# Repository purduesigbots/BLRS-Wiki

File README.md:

---
description: Welcome to the public Purdue SIGBots wiki and knowledge base!
---

# Welcome!

<table data-view="cards"><thead><tr><th></th><th></th><th></th><th data-hidden data-card-cover data-type="files"></th><th data-hidden data-card-target data-type="content-ref"></th></tr></thead><tbody><tr><td></td><td>VEX Drivetrains</td><td></td><td><a href=".gitbook/assets/drive.JPG">drive.JPG</a></td><td><a href="hardware/vex-drivetrains/">vex-drivetrains</a></td></tr><tr><td></td><td>Odometry</td><td></td><td><a href=".gitbook/assets/track.jpg">track.jpg</a></td><td><a href="software/odometry.md">odometry.md</a></td></tr><tr><td></td><td>Game Analysis</td><td></td><td><a href=".gitbook/assets/images (1).jpg">images (1).jpg</a></td><td><a href="judging/notion/purdue-sigbots-notion-template/game-analysis.md">game-analysis.md</a></td></tr></tbody></table>

## Getting started with VEX Robotics?

Here on the Purdue SIGBots Wiki, you will find a place to grow your robotics knowledge. Whether you need to start a club with our [Team Financials](https://wiki.purduesigbots.com/team-administration/team-finances) article, or you want to learn some more about programming with our [Odometry](https://wiki.purduesigbots.com/software/odometry) article, there is more to learn here.

The wiki was created to host the knowledge of the VEX community with resources for competitors at all levels. It started with years of SIGBots documentation but has expanded with many open-source contributors, and new articles always being added. The wiki will stay up to date with new knowledge and continue to strengthen the articles already published.

If you are interested in contributing to the wiki feel free to open a pull request on the [wiki's repo](https://github.com/purduesigbots/BLRS-Wiki). Simply click edit on GitHub on any of the pages to see where in the repo that specific page is. We also allow contributions by PDF and Word Documents, so check it out under [contributing guidelines.](contributing-guidelines/)

If you would like to discuss or bring up an issue with the wiki without fixing it yourself, feel free to open up an issue on the aforementioned [wiki repo](https://github.com/purduesigbots/BLRS-Wiki).

<figure><figcaption><p>2024 World Champions</p></figcaption></figure>

As always if you have any questions or concerns feel free to contact us at: [sig.robotics.purdue@gmail.com](mailto:Sig.robotics.purdue@gmail.com). Please CC your coach in the email to help us assist you more effectively.

.png>)

This work is licensed under a [Creative Commons Attribution-ShareAlike 2.0 Generic License](https://creativecommons.org/licenses/by-sa/2.0/).

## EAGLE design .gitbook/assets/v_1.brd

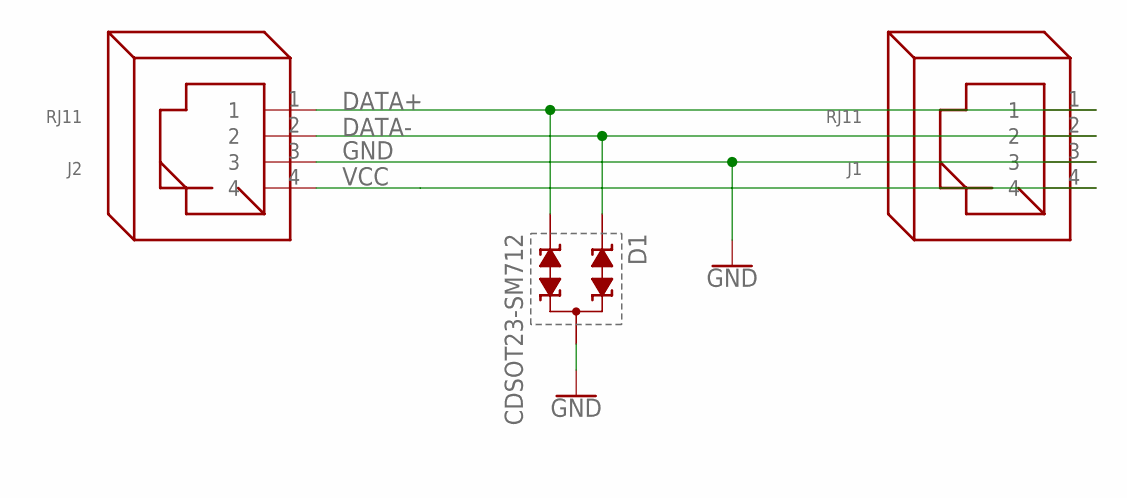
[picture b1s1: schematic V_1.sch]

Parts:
D1: CDSOT23-SM712; SOT23
J1, J2: RJ11

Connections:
DATA+: D1.2, J1.1, J2.1
DATA-: D1.1, J1.2, J2.2
GND: D1.3, J1.3, J2.3
VCC: J1.4, J2.4

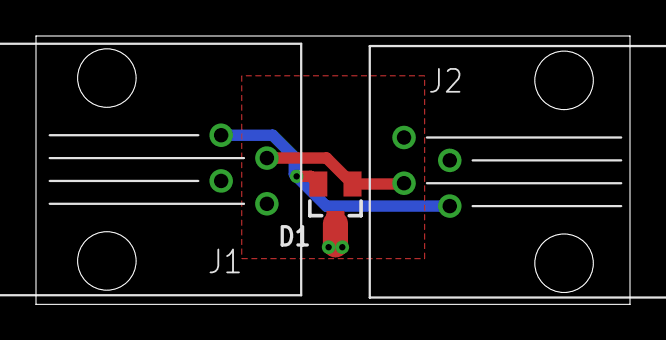
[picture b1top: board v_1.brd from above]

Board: 2 copper layers, 33.0 x 14.9 mm, 3 parts (0 on the bottom side), 4 nets.

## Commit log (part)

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2020-05-26 vex related version control info
2020-05-26 grammar
2020-05-27 GitBook: [master] 2 pages modified
2020-05-29 GitBook: [master] 4 pages and one asset modified
2020-05-29 GitBook: [master] one page modified
2020-05-29 GitBook: [master] one page and one asset modified
2020-05-29 GitBook: [master] one page and 2 assets modified
2020-06-02 Create Vex Joints
    First hardware file, explanation of four Vex joints and their uses.
2020-06-02 Add Robot Examples to Vex Joints
    Could not find examples of compact screw joints.
2020-06-02 Created vex-drivetrains.md
2020-06-03 Fixed image names in vex-joints.md
2020-06-03 Changed "bling" to "locked omnis"
2020-06-08 GitBook: [master] 4 pages modified
2020-07-05 GitBook: [master] 124 pages and 14 assets modified
2020-07-05 fix weird url
2020-07-05 Revert "fix weird url"
    This reverts commit 62ea0944f2e579705343a0490e4b66579ec3d277.
2020-07-05 try fix again
2020-07-05 GitBook: [master] 31 pages and 14 assets modified
2020-07-05 fix bad links
2020-07-06 Pulled the mechanics wiki pages from phabricator
2020-07-16 Add the photos from Phabricator
2020-07-27 Adding Hardware Articles
2020-07-27 GitBook: [master] 14 pages modified
2020-07-27 Added Examples to Flipout Mechanisms.md
2020-07-28 GitBook: [master] 2 pages and 3 assets modified
2020-07-28 GitBook: [master] 5 pages modified
2020-08-06 Update four-bar.md
    Removed the mention of the SIGBots' Nothing But Net robot.
2020-08-06 Fixed images on Flip Out Mechanisms
2020-08-25 Modify format.sh
    - Change shebang to '#!/bin/sh'
    - refactor if else statements
    - Double quote filename variables
2020-09-13 Add new workflow section on pushing an existing project
2020-10-17 Began the work on the pros and cons section of the catapult page.1
2021-01-28 GitBook: [master] 106 pages modified
2021-02-13 GitBook: [master] 2 pages and 5 assets modified
2021-02-15 New Laser Distance Sensor Article
    Basically just ToF being added for lasers. Check on the velocity explanation, I didn't know how to accurately depict it in a non-mathematical way.
2021-02-15 Fix typo in other-lifts.md
    "Turning Point" -> "Tower Takeover"
2021-02-16 Added untracked file
2021-02-16 Added optical sensor to index
2021-02-16 GitBook: [master] 7 pages and 14 assets modified
2021-02-20 Update distance-sensor
2021-02-20 GitBook: [master] 4 pages and 10 assets modified
2021-02-27 GitBook: [master] 109 pages modified
2021-03-19 GitBook: [master] 109 pages and one asset modified
2021-05-23 GitBook: [master] 6 pages and 3 assets modified
2021-05-23 Revert commit
2021-05-23 Added Untracked Images
2021-05-23 GitBook: [master] 6 pages modified
2021-06-04 GitBook: [master] 110 pages and one asset modified
2021-06-09 GitBook: [master] 112 pages and 2 assets modified
2021-06-10 GitBook: [master] 2 pages and 2 assets modified
2021-06-19 GitBook: [master] 3 pages modified
2021-06-21 GitBook: [master] 113 pages modified
2021-06-22 GitBook: [master] one page and 6 assets modified
2021-06-30 attempting an update on the kalman article
2021-07-25 finished adding unedited content, a bit of editing
2021-07-27 GitBook: [master] 49 pages and 191 assets modified
2021-08-08 editing and final polish
2021-09-28 GitBook: [master] 160 pages and 3 assets modified
2021-10-06 GitBook: [master] 14 pages and 61 assets modified
2021-10-14 GitBook: [#341] Getting Started with VEX thread (still updating)
2021-10-26 GitBook: [#343] Potentiometer article updates (still updating)
2021-10-27 GitBook: [#366] Fixed image formatting
2021-10-27 GitBook: [#367] Quickly Discuss JLC Coupons for Less Confusion and Clearer Instructions
2021-11-01 GitBook: [#364] odometry page creation (done)
2022-01-12 GitBook: [#371] How to Start a Notebook
2022-01-12 GitBook: [#379] Update ESD Boards With Ground Planes
2022-01-22 GitBook: [#337] VEX GPS Sensor Actual Work
2022-01-24 GitBook: [#382] Removed Photos of Notebook Rubric
2022-02-16 GitBook: [#368] Team Administration Section Master Branch
2022-02-16 GitBook: [#385] Interview
2022-02-16 GitBook: [#388] No subject
2022-02-17 Added tips on how to gain sponsors for VEX teams
2022-02-17 GitBook: [#391] Remove First and Second Person from Sponsor Article
2022-03-23 GitBook: [#377] Basic Pure Pursuit Guide Port
2022-04-20 GitBook: [#396] Six Bar Updating
2022-04-22 GitBook: [#405] Deleted Getting Started with Vex from Contributing Guidelines
2022-04-28 GitBook: [#394] Max's Fire Updates
2022-05-05 GitBook: [#406] Worlds Livestream Archive
2022-05-13 GitBook: [#408] Livestream Archive Updates
2022-05-20 GitBook: [#410] Team Finances Bug Fix
2022-05-23 remove the grid system article
2022-05-23 first draft of ramsete article
2022-05-24 add an article on basic filtering techniques
2022-05-25 update summary
2022-05-25 GitBook: [#412] RAMSETE Merge Fix?
2022-05-25 GitBook: [#418] Fix the inline math things for the ramsete article
2022-05-28 GitBook: [#420] RAMSETE Text-Within-LaTeX-Block Rev
2022-06-03 GitBook: [#423] Add a V5 Motor Current Limiting section
2022-06-03 GitBook: [#428] No subject
2022-06-06 GitBook: [#431] VexCAD - Scuff Controller
2022-06-08 GitBook: [#433] odom dark mode diagram fix
2022-06-09 GitBook: [#432] DC Motor Basics
2022-06-16 GitBook: [#437] Remove misplaced graph
2022-06-19 GitBook: [#438] Team Documentation > Integrating Inventor Models into Documentation
2022-07-09 GitBook: [#440] Gyroscope, Ultrasonic, Vision, & Distance Sensor Revisions; LED Indicator Article (+ minor fixes)
2022-07-26 Fix keyboard shortcut for visibility
2022-07-31 GitBook: [#441] Jacob's Fire Edits (interview & notebook)
2022-08-05 GitBook: [#444] 3-Wire Expander Article, Gyroscope Updates, Icon Polishing + other fixes
2022-09-08 GitBook: [#447] Fusion Drivetrain
2022-09-27 GitBook: [#402] Bug fix in software and update to allow for future pushes. Gitbook bad
2022-10-11 GitBook: [#453] Take Back Half
2022-10-12 GitBook: [#451] Inventor 1.4
2022-10-14 GitBook: [#407] Removing First and Second Person Language from Odom Port (Pure Pursuit to come)
2022-10-21 GitBook: [#455] Welcome and Mission Statement changes
2022-10-30 GitBook: [#459] Smaller Wiki Logo and Worlds Team Photo
2022-10-31 GitBook: [#411] Hosting Competitions
2022-11-01 GitBook: [#460] No subject
2022-11-10 Revert "Update live-streaming.md"
2022-11-15 GitBook: [#469] Ramsete Correction - Closes #44
2022-11-24 GitBook: [#470] Livestream spelling and footer bc Grammarly doesn't work on GitHub
2022-11-25 GitBook: [#472] No subject
2022-11-25 GitBook: [#473] No subject
2022-11-30 GitBook: [#477] No subject
2022-12-25 GitBook: [#479] Software Basics Section (and reorganizing software)
2022-12-25 GitBook: [#481] Attribution and Typo Fixes
2022-12-25 GitBook: [#443] Lift Gifs bc I don't want to wait for more renders
2023-01-01 GitBook: [#487] Part Library Hint
2023-01-31 Minor Correction To LocalOffset Equation
    From my own testing as well as referencing the OKApi code here https://github.com/OkapiLib/OkapiLib/blob/master/src/api/odometry/threeEncoderOdometry.cpp, I believe one of theta's should be a deltaTh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
2023-02-07 GITBOOK-489: Defensive Wings - for Jonathan
2023-03-05 Update odometry.md
    Fixed formatting errors in equation 6, added suggestion to keep the cycle time not too low.
2023-03-15 GITBOOK-491: Introduction to VEX Parts > Motion > Mecanum Wheels
2023-03-17 GITBOOK-492: Introduction to VEX Parts > Motion > Omnidirectional Wheels
2023-03-29 GITBOOK-484: Drivetrain Updates
2023-03-31 GITBOOK-494: Worlds Interview Leak
2023-03-31 GITBOOK-495: spelling fixes from 1am
2023-03-31 GITBOOK-496: removing worlds interview for Kunwar
2023-04-20 GITBOOK-500: Livestream Updates
2023-04-23 GITBOOK-497: Jacob's Fire Additions
2023-05-03 changed file names and testing HTML
2023-05-03 remove test. RIP Client
2023-05-15 GITBOOK-505: change request with no subject merged in GitBook
2023-05-18 GITBOOK-506: Worlds Livestream Archive Updates
2023-05-19 GITBOOK-508: RTB fixes/improvements (small)
2023-06-03 GITBOOK-504: Add Cheesy Drive Article
2023-06-03 GITBOOK-513: Test
2023-06-04 GITBOOK-515: revision whirlwind
2023-06-04 GITBOOK-516: fix missing hyphen in livestream article
2023-10-10 GITBOOK-528: Add 5.5w motor specs
2023-12-08 GITBOOK-532: PID Article Revamp
2023-12-28 GITBOOK-534: Notion Video Upload
2023-12-28 GITBOOK-535: I didn’t save before the last push
2023-12-31 GITBOOK-539: Changing Fusion 360 page to reflect new library
2024-01-05 GITBOOK-540: Adding Example Notion Notebooks
2024-03-25 GITBOOK-545: RTB - New Fusion Embeds
2024-04-18 Fixed image in path-planning
2024-04-18 Fixed image name (hopefully)
2024-05-03 GITBOOK-488: Image Substitution: VEX Images -> CAD Renders (Wave 1); Various Revisions
2024-05-03 GITBOOK-457: Flywheel control article
2024-05-03 GITBOOK-541: adding 4-bar banding
2024-05-03 GITBOOK-554: Code Style Guide Part Deux
2024-05-03 GITBOOK-555: Reorg a few of the articles in the software section
2024-05-03 GITBOOK-557: Slight typo
2024-05-03 GITBOOK-558: Another typo whoops
2024-05-03 GITBOOK-560: Fix up a section header to be more specific (multiple files)
2024-05-03 GITBOOK-561: Typo (notha one)
2024-05-03 GITBOOK-562: Unboomerize Code Styling Guide (Stephen Carlson or Jonathan)
2024-05-14 GITBOOK-567: fixing broken links
2024-05-15 GITBOOK-568: Porting over the OSRC changes to gitbook. (PR#55)
2024-05-16 GITBOOK-565: VexU Article
2024-05-16 GITBOOK-570: add wheel video
2024-05-16 GITBOOK-572: center of mass
2024-05-16 GITBOOK-573: Adding BLRS2 Notebooks
2024-05-17 GITBOOK-576: update welcome page for high stakes
2024-05-18 GITBOOK-575: example of base jump for com & 4-bar changes
2024-05-23 GITBOOK-577: Fixing Notebook Download Link
2024-05-25 GITBOOK-579: Add Warnings at the Each of the worlds livestream pages
2024-05-28 GITBOOK-580: How *not* to run a team article
2024-05-28 GITBOOK-582: Reword a phrase that was badly worded
2024-05-28 GITBOOK-583: Fix to another unfinished sentence.
2024-07-09 GITBOOK-589: Rearranging the judging process
2024-07-23 GITBOOK-590: Max's July Changes
2024-07-24 GITBOOK-591: C++ Basics For VEX Robotics
2024-08-06 GITBOOK-595: moving mecanum stuff
2024-08-06 GITBOOK-564: improving drivetrain design
2024-08-06 GITBOOK-597: improve drivetrain design again
2024-08-18 GITBOOK-593: horizontal com location
2024-08-19 fixed typo again
    :/
2024-09-03 GITBOOK-601: adding cascade example
2024-09-05 GITBOOK-602: change request with no subject merged in GitBook
2024-09-05 GITBOOK-604: Fix attribution in the solidworks article
2024-09-29 Update SUMMARY to include vexide article
2024-10-28 GITBOOK-600: Add Worlds 2024 to Livestream Archive
2024-11-08 remove specific installation instructions for vexide
2024-12-04 GITBOOK-605: moving plastic manufacturing
2024-12-04 GITBOOK-606: scuff controller versions
2024-12-05 GITBOOK-609: update pros info
2024-12-05 GITBOOK-610: update pros again
2024-12-06 GITBOOK-608: add pid examples
2025-02-28 simple LaTeX fixes for odometry.md
2025-03-04 GITBOOK-612: nesting plastic
2025-04-07 GITBOOK-616: consistency type setting
2025-06-01 GITBOOK-617: update title page
2025-06-24 Fixed my_functions.hpp & my_functions.cpp ex. files
    my_functions.hpp now has #include "pros/motors.hpp" which is needed to compile.
    my_functions.cpp now configures the motor with a port, rather than attempting to create a motor with no parameters.
    Both of these changes are necessary to compile the example files.
2025-06-26 GITBOOK-619: 2" omni clocking positions
2025-08-28 GITBOOK-618: Jacob's Fire Judging Edits
2026-01-09 Revise vexide documentation and enhance features list
2026-01-11 Add related links to vexide page
2026-01-11 Remove redundant word
2026-01-11 More community notebooks
    added 3 new notebooks (3249U, 1469A, Diana Gale). All of these are very strong and detailed notebooks, and come with a lot of info on formatting, documentation, etc.
    Contributed by Nicole (currently no team, formerly 95071V)
2026-03-05 GITBOOK-623: updated license plate rules
2026-04-28 Add warning about metal coloring legality for VEX
    Added a warning about the legality of coloring metals for VEX Override in 2026-27.
2026-04-28 Add warning about dyeing VEX parts legality
    Added a warning about the legality of dyeing VEX parts for the 2026-27 season.
2026-05-18 improve clarity and fix error in 5.5w motor toque spec

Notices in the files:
parts and their libraries:
SparkFun-PowerSymbols: Licensing: Creative Commons ShareAlike 4.0 International - https://creativecommons.org/licenses/by-sa/4.0
